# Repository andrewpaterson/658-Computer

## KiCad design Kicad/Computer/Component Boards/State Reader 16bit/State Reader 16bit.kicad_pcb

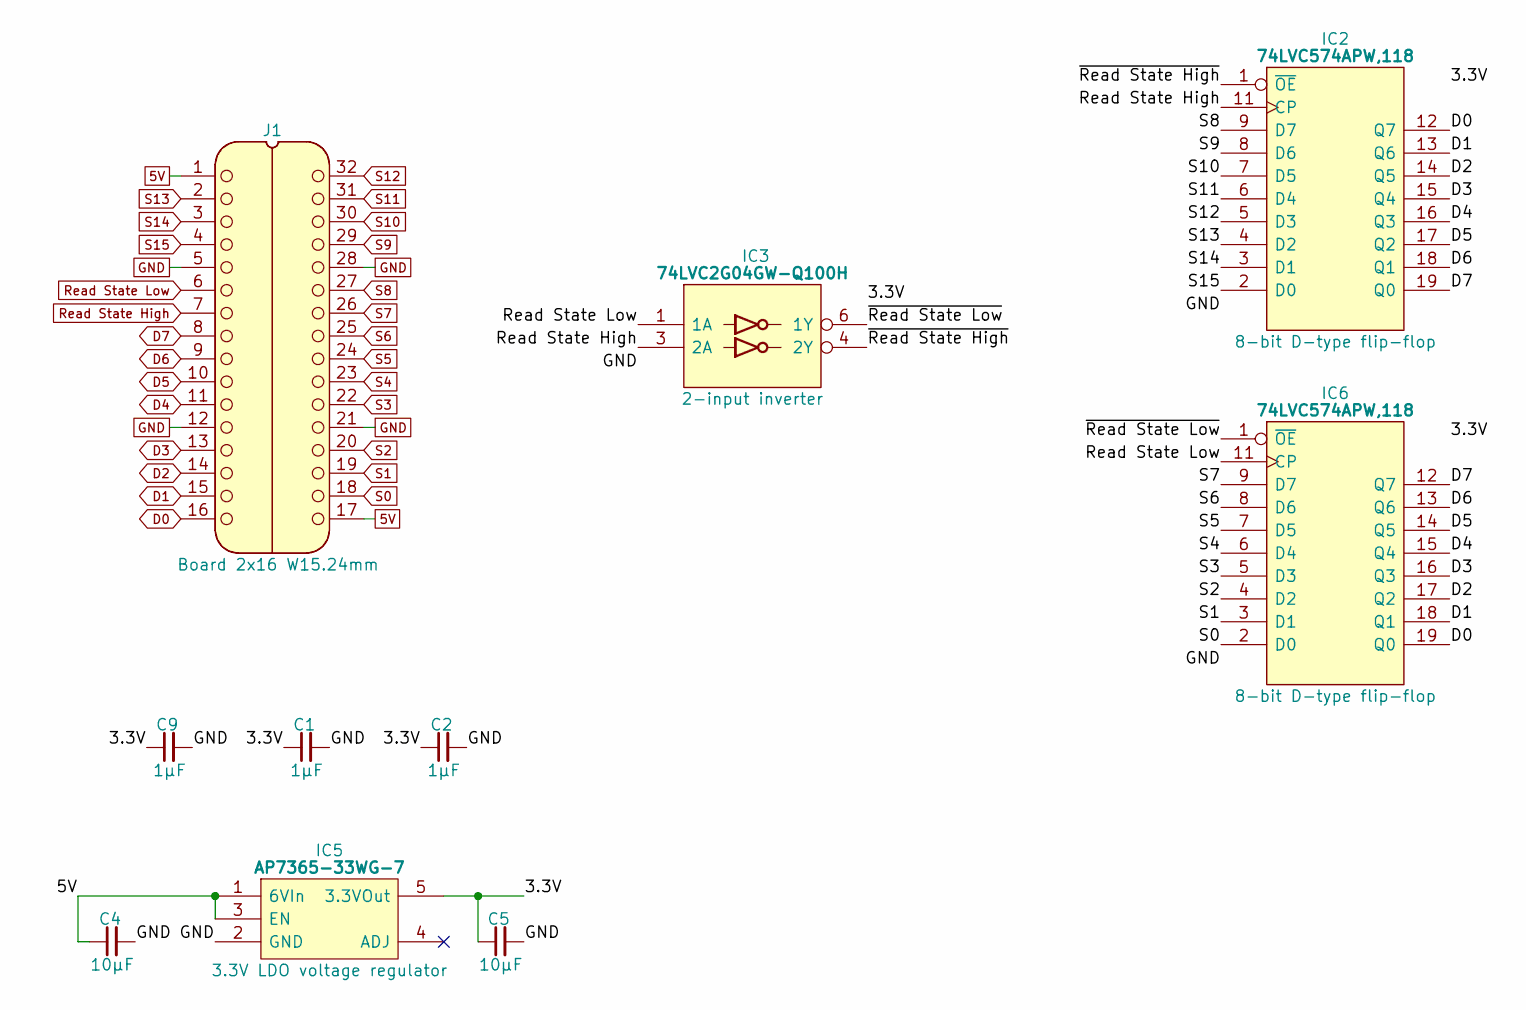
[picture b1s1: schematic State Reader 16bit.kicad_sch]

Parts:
C1, C2, C9: 1μF; C_0805
C4, C5: 10µF; C_0805
IC2, IC6: 74LVC574APW,118; SOP65P640X110-20N; Mouser Part Number 771-74LVC574APW-T
IC3: 74LVC2G04GW-Q100H; SOP65P210X110-6N; Manufacturer_Part_Number 74LVC2G04GW-Q100H; Mouser Part Number 771-74LVC2G04GWQ100H
IC5: AP7365-33WG-7; SOT95P285X130-5N; Manufacturer_Part_Number AP7365-33WG-7; Mouser Part Number 621-AP7365-33WG-7
J1: Board 2x16 W15.24mm; DIP-32_Board_W15.24mm

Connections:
5V: C4.1, IC5.1 (6VIn), IC5.3 (EN), J1.1, J1.17
/3.3V: C1.1, C2.1, C5.1, C9.1, IC2.20 (3V), IC3.5 (3V), IC5.5 (3.3VOut), IC6.20 (3V)
/~Read State High: IC2.1 (~OE), IC3.4 (2Y)
/~Read State Low: IC3.6 (1Y), IC6.1 (~OE)
D0: IC2.12 (Q7), IC6.19 (Q0), J1.16
D1: IC2.13 (Q6), IC6.18 (Q1), J1.15
D2: IC2.14 (Q5), IC6.17 (Q2), J1.14
D3: IC2.15 (Q4), IC6.16 (Q3), J1.13
D4: IC2.16 (Q3), IC6.15 (Q4), J1.11
D5: IC2.17 (Q2), IC6.14 (Q5), J1.10
D6: IC2.18 (Q1), IC6.13 (Q6), J1.9
D7: IC2.19 (Q0), IC6.12 (Q7), J1.8
GND: C1.2, C2.2, C4.2, C5.2, C9.2, IC2.10 (GND), IC3.2 (GND), IC5.2 (GND), IC6.10 (GND), J1.5, J1.12, J1.21, J1.28
Read State High: IC2.11 (CP), IC3.3 (2A), J1.7
Read State Low: IC3.1 (1A), IC6.11 (CP), J1.6
S0: IC6.2 (D0), J1.18
S1: IC6.3 (D1), J1.19
S2: IC6.4 (D2), J1.20
S3: IC6.5 (D3), J1.22
S4: IC6.6 (D4), J1.23
S5: IC6.7 (D5), J1.24
S6: IC6.8 (D6), J1.25
S7: IC6.9 (D7), J1.26
S8: IC2.9 (D7), J1.27
S9: IC2.8 (D6), J1.29
S10: IC2.7 (D5), J1.30
S11: IC2.6 (D4), J1.31
S12: IC2.5 (D3), J1.32
S13: IC2.4 (D2), J1.2
S14: IC2.3 (D1), J1.3
S15: IC2.2 (D0), J1.4

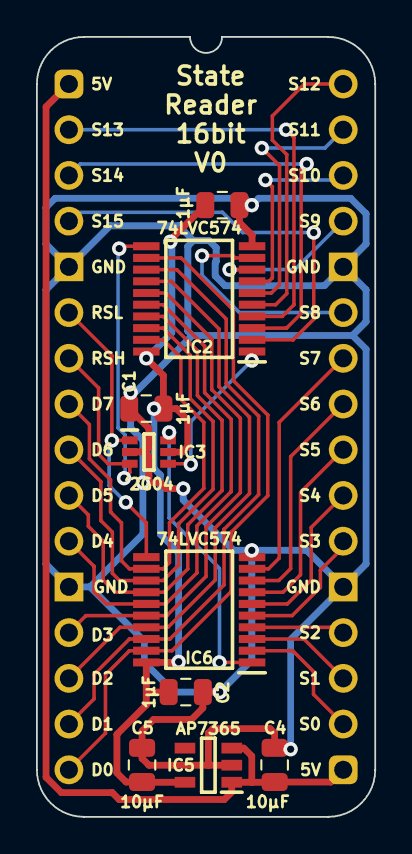
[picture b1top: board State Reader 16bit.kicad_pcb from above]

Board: 2 copper layers, 18.8 x 43.3 mm, 10 parts (0 on the bottom side), 31 nets.

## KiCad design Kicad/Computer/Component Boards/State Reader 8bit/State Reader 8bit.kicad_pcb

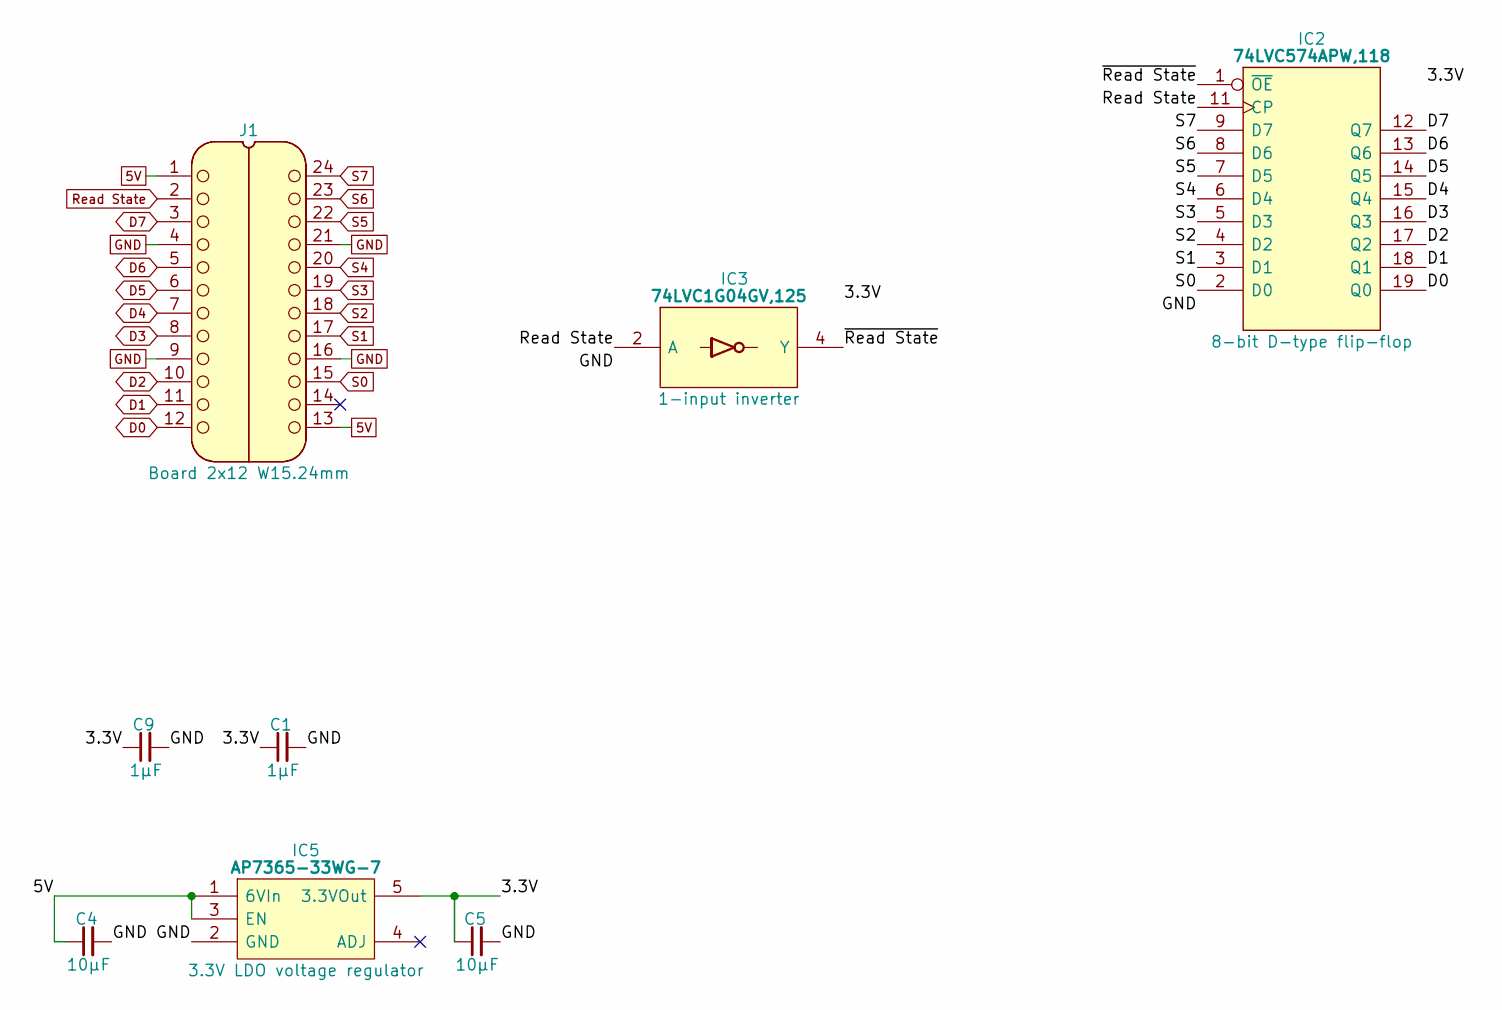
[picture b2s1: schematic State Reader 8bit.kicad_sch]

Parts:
C1, C9: 1μF; C_0805
C4, C5: 10µF; C_0805
IC2: 74LVC574APW,118; SOP65P640X110-20N; Mouser Part Number 771-74LVC574APW-T
IC3: 74LVC1G04GV,125; SOT95P275X110-5N; Manufacturer_Part_Number 74LVC1G04GV,125; Mouser Part Number 771-74LVC1G04GV
IC5: AP7365-33WG-7; SOT95P285X130-5N; Manufacturer_Part_Number AP7365-33WG-7; Mouser Part Number 621-AP7365-33WG-7
J1: Board 2x12 W15.24mm; DIP-24_Board_W15.24mm

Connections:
5V: C4.1, IC5.1 (6VIn), IC5.3 (EN), J1.1, J1.13
/3.3V: C1.1, C5.1, C9.1, IC2.20 (3V), IC5.5 (3.3VOut)
/~Read State: IC2.1 (~OE), IC3.4 (Y)
D0: IC2.19 (Q0), J1.12
D1: IC2.18 (Q1), J1.11
D2: IC2.17 (Q2), J1.10
D3: IC2.16 (Q3), J1.8
D4: IC2.15 (Q4), J1.7
D5: IC2.14 (Q5), J1.6
D6: IC2.13 (Q6), J1.5
D7: IC2.12 (Q7), J1.3
GND: C1.2, C4.2, C5.2, C9.2, IC2.10 (GND), IC3.3 (GND), IC5.2 (GND), J1.4, J1.9, J1.16, J1.21
Read State: IC2.11 (CP), IC3.2 (A), J1.2
S0: IC2.2 (D0), J1.15
S1: IC2.3 (D1), J1.17
S2: IC2.4 (D2), J1.18
S3: IC2.5 (D3), J1.19
S4: IC2.6 (D4), J1.20
S5: IC2.7 (D5), J1.22
S6: IC2.8 (D6), J1.23
S7: IC2.9 (D7), J1.24

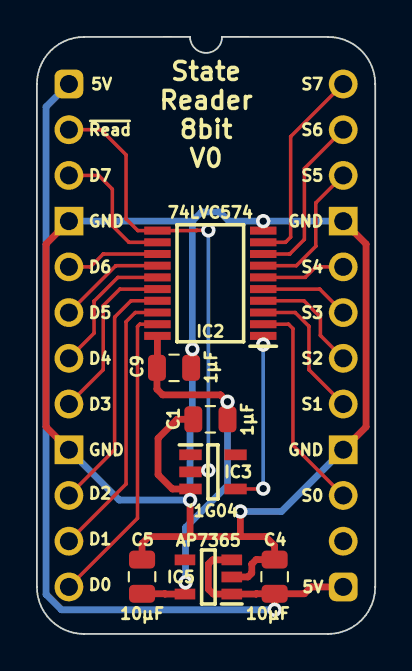
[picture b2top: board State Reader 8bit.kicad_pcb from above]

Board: 2 copper layers, 18.8 x 33.2 mm, 8 parts (0 on the bottom side), 21 nets.

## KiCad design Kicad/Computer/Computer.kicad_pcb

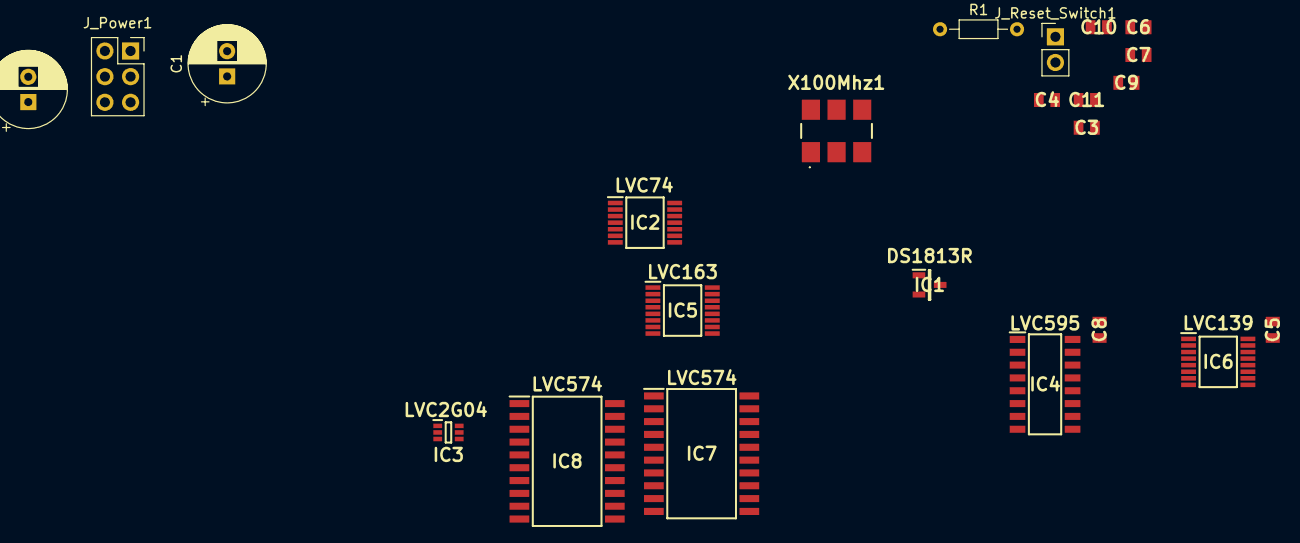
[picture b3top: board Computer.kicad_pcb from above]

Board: 2 copper layers, 23 parts (0 on the bottom side), 5 nets, no tracks yet.

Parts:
C1, C2: CP1000uF; CP_Radial_D7.5mm_P2.50mm
C3: 100pF MLCC; CAPC2012X90N
C4, C5, C6, C7, C8, C9, C10, C11: 1000pF MLCC; CAPC2012X90N
IC1: DS1813R; SOT95P237X112-3N
IC2: LVC74; SOP65P640X110-14N
IC3: LVC2G04; SOP65P210X110-6N
IC4: LVC595; SOIC127P600X175-16N
IC5: LVC163; SOP65P640X110-16N
IC6: LVC139; SOP65P640X110-16N
IC7, IC8: LVC574; SOIC127P1032X265-20N
J_Power1: Conn_02x03; PinSocket_2x03_P2.54mm_Vertical
J_Reset_Switch1: Conn_01x02_Male; PinHeader_1x02_P2.54mm_Vertical
R1: R; R_Axial_DIN0204_L3.6mm_D1.6mm_P7.62mm_Horizontal
X100Mhz1: XLH735100.000000I; XLH735100000000I

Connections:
/Timing Circuit/3.3V: C1.1, C3.1, C4.1, C5.1, C6.1, C7.1, C8.1, C9.1, C10.1, C11.1, IC2.14 (VCC), IC3.5 (VCC), IC4.16 (VCC), IC5.16 (VCC), IC6.16 (VCC), IC7.20 (VCC), IC8.20 (VCC), J_Power1.3, J_Power1.4, X100Mhz1.6 (VDD)
/Timing Circuit/5V: C2.1, IC1.2 (VCC), J_Power1.5, J_Power1.6
/Timing Circuit/GND: C1.2, C2.2, C3.2, C4.2, C5.2, C6.2, C7.2, C8.2, C9.2, C10.2, C11.2, IC1.3 (GND), J_Power1.1, J_Power1.2, R1.1
/Timing Circuit/RSTB: IC1.1 (~RST), J_Reset_Switch1.2
unnamed: J_Reset_Switch1.1, R1.2

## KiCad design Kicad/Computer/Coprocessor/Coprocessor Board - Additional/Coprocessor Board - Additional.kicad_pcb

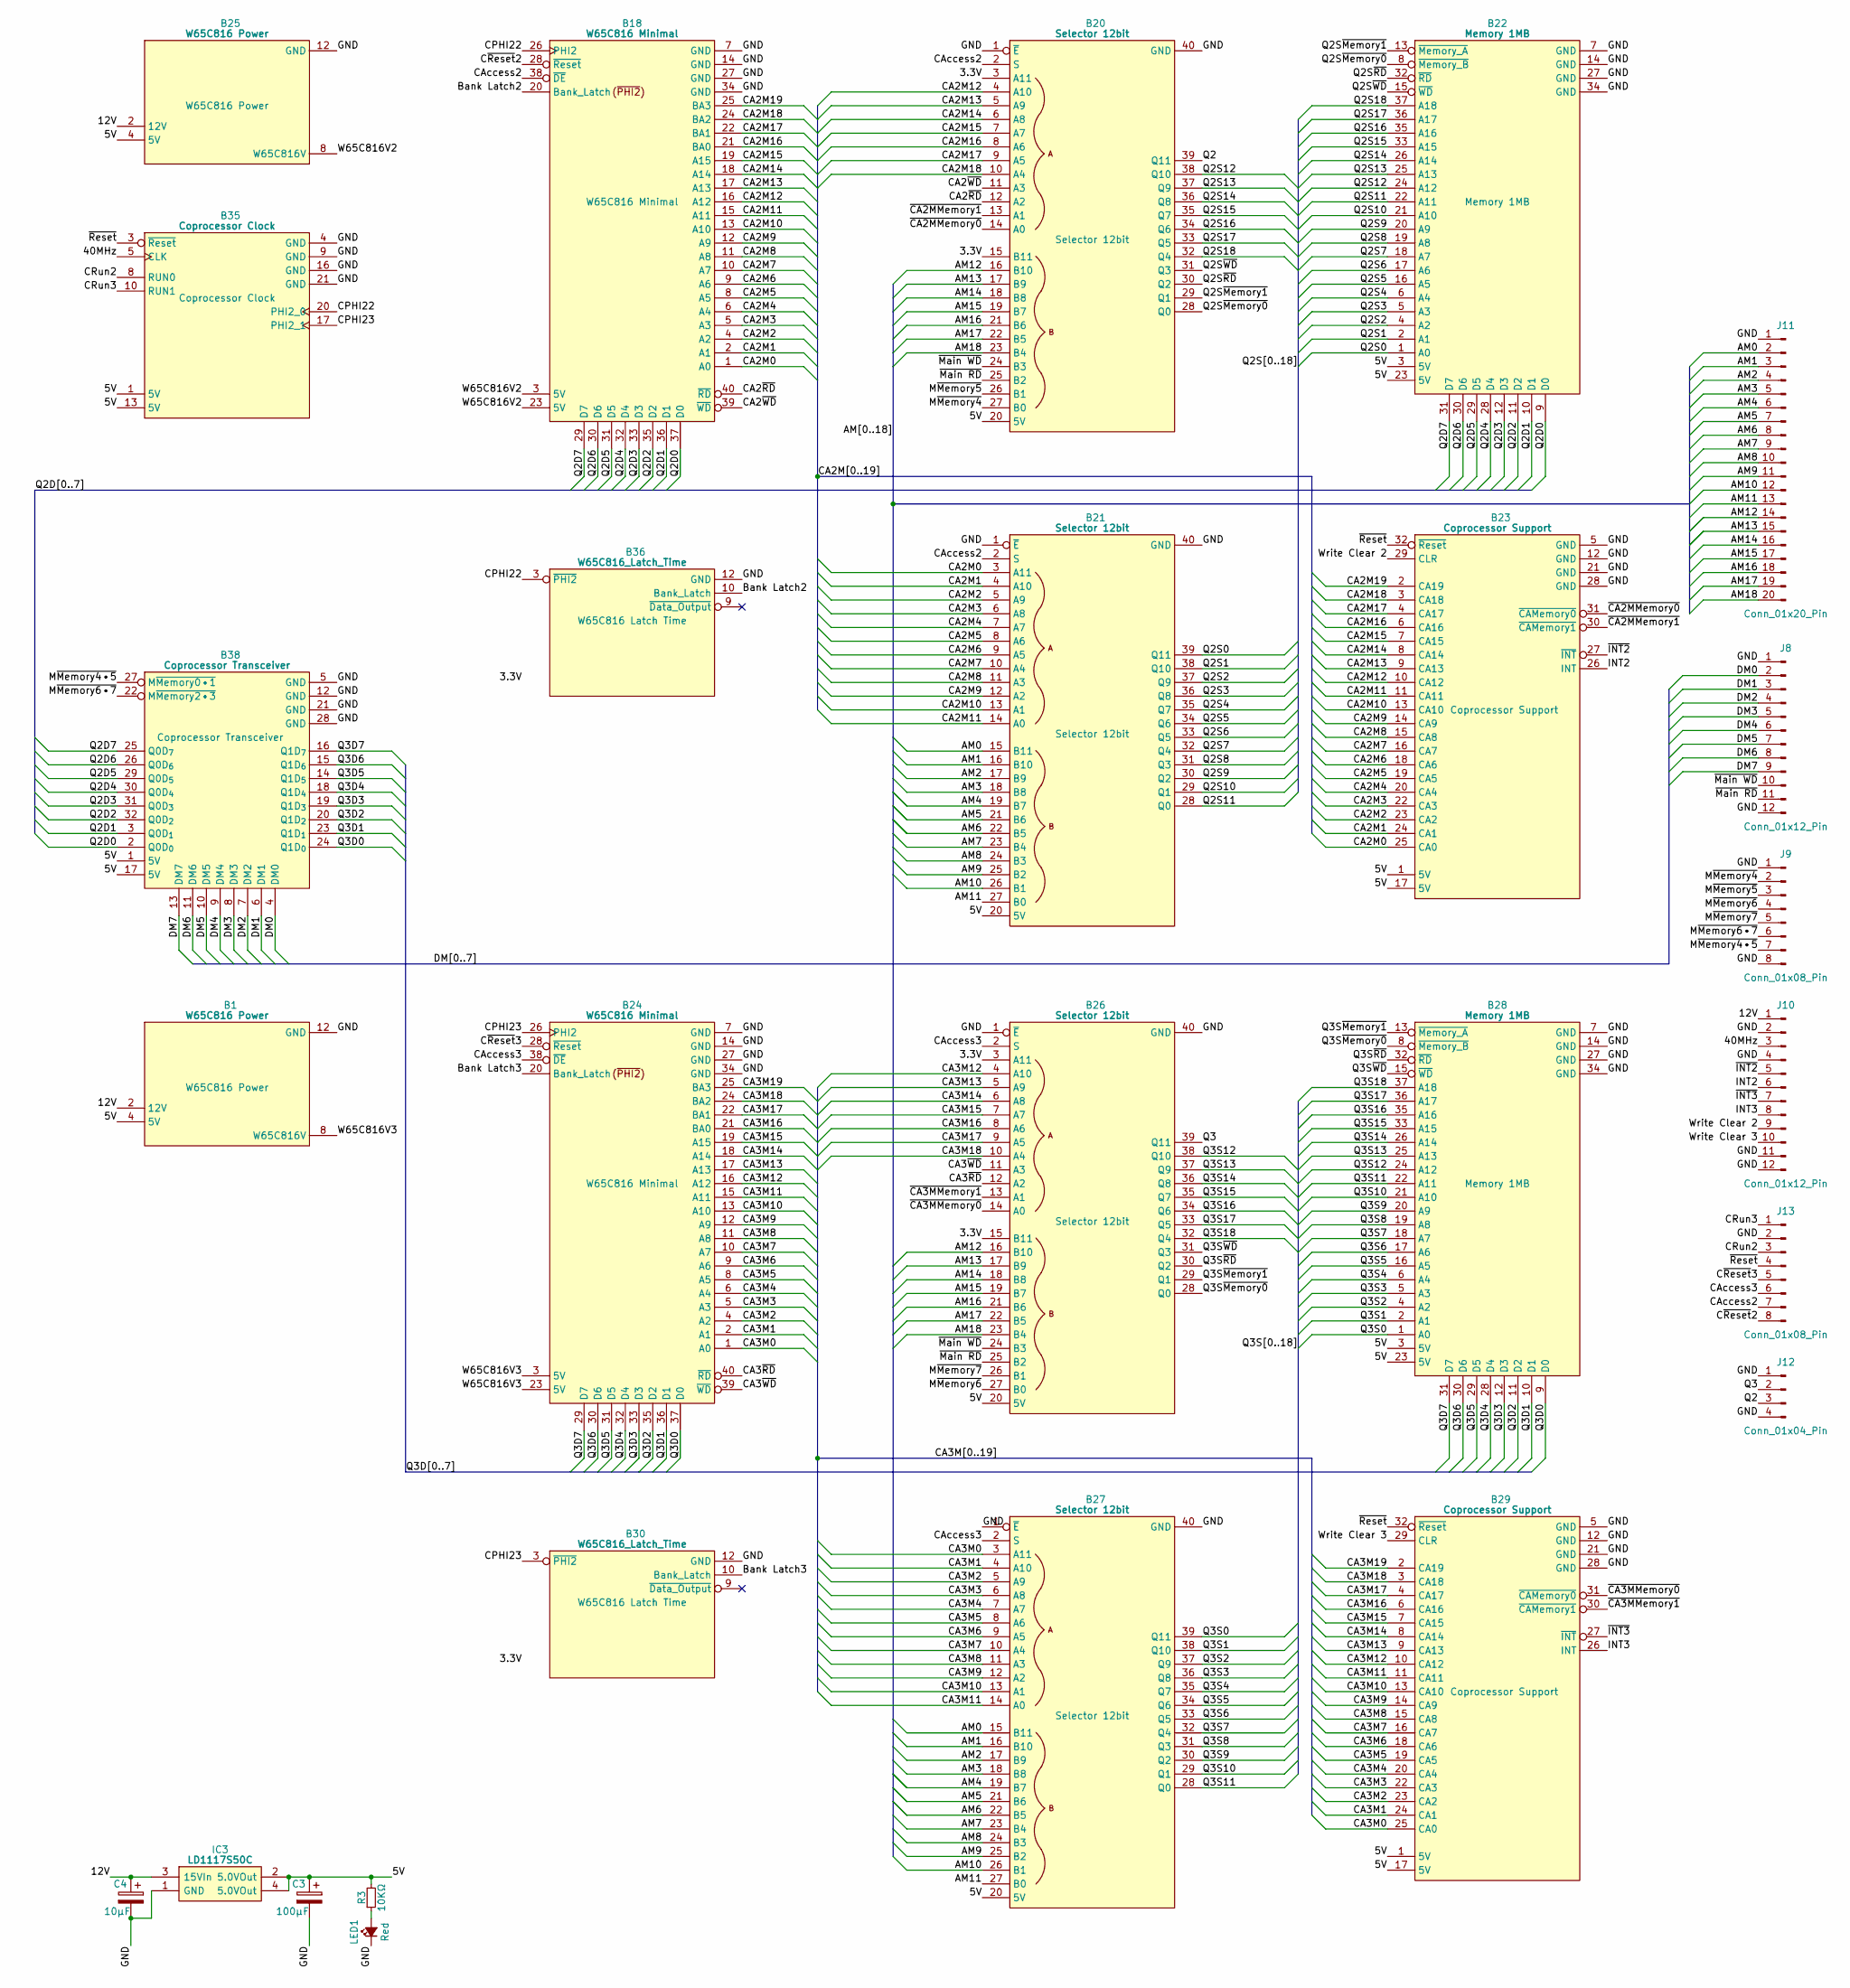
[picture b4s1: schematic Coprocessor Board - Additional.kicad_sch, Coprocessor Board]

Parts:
B1, B25: W65C816 Power; HCP65_W65C816_Power
B18, B24: W65C816 Minimal; HCP65_W65C816_Minimal
B20, B21, B26, B27: Selector 12bit; HCP65_Selector_12bit
B22, B28: Memory 1MB; HCP65_Memory_1MB
B23, B29: Coprocessor Support; HCP65_Coprocessor_Support
B30, B36: W65C816_Latch_Time; HCP65_W65C816_Latch_Time
B35: Coprocessor Clock; HCP65_Coprocessor_Clock
B38: Coprocessor Transceiver; HCP65_Coprocessor_Transceiver
C3: 100μF; CP_Radial_D4.0mm_P2.00mm
C4: 10μF; CP_Radial_D4.0mm_P2.00mm
IC3: LD1117S50C; LD1117S33C; Manufacturer_Part_Number LD1117S50C
J8, J10: Conn_01x12_Pin; PinHeader_1x12_P2.54mm_Vertical
J9, J13: Conn_01x08_Pin; PinHeader_1x08_P2.54mm_Vertical
J11: Conn_01x20_Pin; PinHeader_1x20_P2.54mm_Vertical
J12: Conn_01x04_Pin; PinHeader_1x04_P2.54mm_Vertical
LED1: Red; LED_D5.0mm
R3: 10KΩ; R_0805

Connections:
/3.3V: B20.3 (A11), B20.15 (B11), B26.3 (A11), B26.15 (B11), B30.6 (3.3V), B36.6 (3.3V)
/5V: B1.4 (5V), B20.20 (5V), B21.20 (5V), B22.3 (5V), B22.23 (5V), B23.1 (5V), B23.17 (5V), B25.4 (5V), B26.20 (5V), B27.20 (5V), B28.3 (5V), B28.23 (5V), B29.1 (5V), B29.17 (5V), B35.1 (5V), B35.13 (5V), B38.1 (5V), B38.17 (5V), C3.1, IC3.2 (5.0VOut), IC3.4 (5.0VOut), R3.2
/12V: B1.2 (12V), B25.2 (12V), C4.1, IC3.3 (15VIn), J10.1
/40MHz: B35.5 (CLK), J10.3
/AM0: B21.15 (B11), B27.15 (B11), J11.2
/AM1: B21.16 (B10), B27.16 (B10), J11.3
/AM2: B21.17 (B9), B27.17 (B9), J11.4
/AM3: B21.18 (B8), B27.18 (B8), J11.5
/AM4: B21.19 (B7), B27.19 (B7), J11.6
/AM5: B21.21 (B6), B27.21 (B6), J11.7
/AM6: B21.22 (B5), B27.22 (B5), J11.8
/AM7: B21.23 (B4), B27.23 (B4), J11.9
/AM8: B21.24 (B3), B27.24 (B3), J11.10
/AM9: B21.25 (B2), B27.25 (B2), J11.11
/AM10: B21.26 (B1), B27.26 (B1), J11.12
/AM11: B21.27 (B0), B27.27 (B0), J11.13
/AM12: B20.16 (B10), B26.16 (B10), J11.14
/AM13: B20.17 (B9), B26.17 (B9), J11.15
/AM14: B20.18 (B8), B26.18 (B8), J11.16
/AM15: B20.19 (B7), B26.19 (B7), J11.17
/AM16: B20.21 (B6), B26.21 (B6), J11.18
/AM17: B20.22 (B5), B26.22 (B5), J11.19
/AM18: B20.23 (B4), B26.23 (B4), J11.20
/Bank Latch2: B18.20 (Bank_Latch), B36.10 (Bank_Latch)
/Bank Latch3: B24.20 (Bank_Latch), B30.10 (Bank_Latch)
/CA2M0: B18.1 (A0), B21.3 (A11), B23.25 (CA0)
/CA2M1: B18.2 (A1), B21.4 (A10), B23.24 (CA1)
/CA2M2: B18.4 (A2), B21.5 (A9), B23.23 (CA2)
/CA2M3: B18.5 (A3), B21.6 (A8), B23.22 (CA3)
/CA2M4: B18.6 (A4), B21.7 (A7), B23.20 (CA4)
/CA2M5: B18.8 (A5), B21.8 (A6), B23.19 (CA5)
/CA2M6: B18.9 (A6), B21.9 (A5), B23.18 (CA6)
/CA2M7: B18.10 (A7), B21.10 (A4), B23.16 (CA7)
/CA2M8: B18.11 (A8), B21.11 (A3), B23.15 (CA8)
/CA2M9: B18.12 (A9), B21.12 (A2), B23.14 (CA9)
/CA2M10: B18.13 (A10), B21.13 (A1), B23.13 (CA10)
/CA2M11: B18.15 (A11), B21.14 (A0), B23.11 (CA11)
/CA2M12: B18.16 (A12), B20.4 (A10), B23.10 (CA12)
/CA2M13: B18.17 (A13), B20.5 (A9), B23.9 (CA13)
/CA2M14: B18.18 (A14), B20.6 (A8), B23.8 (CA14)
/CA2M15: B18.19 (A15), B20.7 (A7), B23.7 (CA15)
/CA2M16: B18.21 (BA0), B20.8 (A6), B23.6 (CA16)
/CA2M17: B18.22 (BA1), B20.9 (A5), B23.4 (CA17)
/CA2M18: B18.24 (BA2), B20.10 (A4), B23.3 (CA18)
/CA2M19: B18.25 (BA3), B23.2 (CA19)
/CA2~RD: B18.40 (~RD), B20.12 (A2)
/CA2~WD: B18.39 (~WD), B20.11 (A3)
/CA3M0: B24.1 (A0), B27.3 (A11), B29.25 (CA0)
/CA3M1: B24.2 (A1), B27.4 (A10), B29.24 (CA1)
/CA3M2: B24.4 (A2), B27.5 (A9), B29.23 (CA2)
/CA3M3: B24.5 (A3), B27.6 (A8), B29.22 (CA3)
/CA3M4: B24.6 (A4), B27.7 (A7), B29.20 (CA4)
/CA3M5: B24.8 (A5), B27.8 (A6), B29.19 (CA5)
/CA3M6: B24.9 (A6), B27.9 (A5), B29.18 (CA6)
/CA3M7: B24.10 (A7), B27.10 (A4), B29.16 (CA7)
/CA3M8: B24.11 (A8), B27.11 (A3), B29.15 (CA8)
/CA3M9: B24.12 (A9), B27.12 (A2), B29.14 (CA9)
/CA3M10: B24.13 (A10), B27.13 (A1), B29.13 (CA10)
/CA3M11: B24.15 (A11), B27.14 (A0), B29.11 (CA11)
/CA3M12: B24.16 (A12), B26.4 (A10), B29.10 (CA12)
/CA3M13: B24.17 (A13), B26.5 (A9), B29.9 (CA13)
/CA3M14: B24.18 (A14), B26.6 (A8), B29.8 (CA14)
/CA3M15: B24.19 (A15), B26.7 (A7), B29.7 (CA15)
/CA3M16: B24.21 (BA0), B26.8 (A6), B29.6 (CA16)
/CA3M17: B24.22 (BA1), B26.9 (A5), B29.4 (CA17)
/CA3M18: B24.24 (BA2), B26.10 (A4), B29.3 (CA18)
/CA3M19: B24.25 (BA3), B29.2 (CA19)
/CA3~RD: B24.40 (~RD), B26.12 (A2)
/CA3~WD: B24.39 (~WD), B26.11 (A3)
/CAccess2: B18.38 (~DE), B20.2 (S), B21.2 (S), J13.7
/CAccess3: B24.38 (~DE), B26.2 (S), B27.2 (S), J13.6
/CPHI22: B18.26 (PHI2), B35.20 (PHI2_0), B36.3 (~PHI2)
/CPHI23: B24.26 (PHI2), B30.3 (~PHI2), B35.17 (PHI2_1)
/CRun2: B35.8 (RUN0), J13.3
/CRun3: B35.10 (RUN1), J13.1
/C~Reset2: B18.28 (~Reset), J13.8
/C~Reset3: B24.28 (~Reset), J13.5
/DM0: B38.4 (DM0), J8.2
/DM1: B38.6 (DM1), J8.3
/DM2: B38.7 (DM2), J8.4
/DM3: B38.8 (DM3), J8.5
/DM4: B38.9 (DM4), J8.6
/DM5: B38.10 (DM5), J8.7
/DM6: B38.11 (DM6), J8.8
/DM7: B38.13 (DM7), J8.9
/GND: B1.12 (GND), B18.7 (GND), B18.14 (GND), B18.27 (GND), B18.34 (GND), B20.1 (~E), B20.40 (GND), B21.1 (~E), B21.40 (GND), B22.7 (GND), B22.14 (GND), B22.27 (GND), B22.34 (GND), B23.5 (GND), B23.12 (GND), B23.21 (GND), B23.28 (GND), B24.7 (GND), B24.14 (GND), B24.27 (GND), B24.34 (GND), B25.12 (GND), B26.1 (~E), B26.40 (GND), B27.1 (~E), B27.40 (GND), B28.7 (GND), B28.14 (GND), B28.27 (GND), B28.34 (GND), B29.5 (GND), B29.12 (GND), B29.21 (GND), B29.28 (GND), B30.12 (GND), B35.4 (GND), B35.9 (GND), B35.16 (GND), B35.21 (GND), B36.12 (GND), B38.5 (GND), B38.12 (GND), B38.21 (GND), B38.28 (GND), C3.2, C4.2, IC3.1 (GND), J8.1, J8.12, J9.1, J9.8, J10.2, J10.4, J10.11, J10.12, J11.1, J12.1, J12.4, J13.2, LED1.1 (K)
/INT2: B23.26 (INT), J10.6
/INT3: B29.26 (INT), J10.8
/M~Memory4: B20.27 (B0), J9.2
/M~Memory4•5: B38.27 (M~Memory0•1), J9.7
/M~Memory5: B20.26 (B1), J9.3
/M~Memory6: B26.27 (B0), J9.4
/M~Memory6•7: B38.22 (M~Memory2•3), J9.6
/M~Memory7: B26.26 (B1), J9.5
/Q2: B20.39 (Q11), J12.3
/Q2D0: B18.37 (D0), B22.9 (D0), B38.2 (Q0D_{0})
/Q2D1: B18.36 (D1), B22.10 (D1), B38.3 (Q0D_{1})
/Q2D2: B18.35 (D2), B22.11 (D2), B38.32 (Q0D_{2})
/Q2D3: B18.33 (D3), B22.12 (D3), B38.31 (Q0D_{3})
/Q2D4: B18.32 (D4), B22.28 (D4), B38.30 (Q0D_{4})
/Q2D5: B18.31 (D5), B22.29 (D5), B38.29 (Q0D_{5})
/Q2D6: B18.30 (D6), B22.30 (D6), B38.26 (Q0D_{6})
/Q2D7: B18.29 (D7), B22.31 (D7), B38.25 (Q0D_{7})
/Q2S0: B21.39 (Q11), B22.1 (A0)
/Q2S1: B21.38 (Q10), B22.2 (A1)
/Q2S2: B21.37 (Q9), B22.4 (A2)
/Q2S3: B21.36 (Q8), B22.5 (A3)
/Q2S4: B21.35 (Q7), B22.6 (A4)
/Q2S5: B21.34 (Q6), B22.16 (A5)
/Q2S6: B21.33 (Q5), B22.17 (A6)
/Q2S7: B21.32 (Q4), B22.18 (A7)
/Q2S8: B21.31 (Q3), B22.19 (A8)
/Q2S9: B21.30 (Q2), B22.20 (A9)
/Q2S10: B21.29 (Q1), B22.21 (A10)
/Q2S11: B21.28 (Q0), B22.22 (A11)
/Q2S12: B20.38 (Q10), B22.24 (A12)
/Q2S13: B20.37 (Q9), B22.25 (A13)
/Q2S14: B20.36 (Q8), B22.26 (A14)
/Q2S15: B20.35 (Q7), B22.33 (A15)
/Q2S16: B20.34 (Q6), B22.35 (A16)
/Q2S17: B20.33 (Q5), B22.36 (A17)
/Q2S18: B20.32 (Q4), B22.37 (A18)
/Q2S~Memory0: B20.28 (Q0), B22.8 (~Memory_B)
/Q2S~Memory1: B20.29 (Q1), B22.13 (~Memory_A)
/Q2S~RD: B20.30 (Q2), B22.32 (~RD)
/Q2S~WD: B20.31 (Q3), B22.15 (~WD)
/Q3: B26.39 (Q11), J12.2
/Q3D0: B24.37 (D0), B28.9 (D0), B38.24 (Q1D_{0})
/Q3D1: B24.36 (D1), B28.10 (D1), B38.23 (Q1D_{1})
/Q3D2: B24.35 (D2), B28.11 (D2), B38.20 (Q1D_{2})
/Q3D3: B24.33 (D3), B28.12 (D3), B38.19 (Q1D_{3})
/Q3D4: B24.32 (D4), B28.28 (D4), B38.18 (Q1D_{4})
/Q3D5: B24.31 (D5), B28.29 (D5), B38.14 (Q1D_{5})
/Q3D6: B24.30 (D6), B28.30 (D6), B38.15 (Q1D_{6})
/Q3D7: B24.29 (D7), B28.31 (D7), B38.16 (Q1D_{7})
/Q3S0: B27.39 (Q11), B28.1 (A0)
/Q3S1: B27.38 (Q10), B28.2 (A1)
/Q3S2: B27.37 (Q9), B28.4 (A2)
/Q3S3: B27.36 (Q8), B28.5 (A3)
/Q3S4: B27.35 (Q7), B28.6 (A4)
/Q3S5: B27.34 (Q6), B28.16 (A5)
/Q3S6: B27.33 (Q5), B28.17 (A6)
/Q3S7: B27.32 (Q4), B28.18 (A7)
/Q3S8: B27.31 (Q3), B28.19 (A8)
/Q3S9: B27.30 (Q2), B28.20 (A9)
/Q3S10: B27.29 (Q1), B28.21 (A10)
/Q3S11: B27.28 (Q0), B28.22 (A11)
/Q3S12: B26.38 (Q10), B28.24 (A12)
/Q3S13: B26.37 (Q9), B28.25 (A13)
/Q3S14: B26.36 (Q8), B28.26 (A14)
/Q3S15: B26.35 (Q7), B28.33 (A15)
/Q3S16: B26.34 (Q6), B28.35 (A16)
/Q3S17: B26.33 (Q5), B28.36 (A17)
/Q3S18: B26.32 (Q4), B28.37 (A18)
/Q3S~Memory0: B26.28 (Q0), B28.8 (~Memory_B)
/Q3S~Memory1: B26.29 (Q1), B28.13 (~Memory_A)
/Q3S~RD: B26.30 (Q2), B28.32 (~RD)
/Q3S~WD: B26.31 (Q3), B28.15 (~WD)
/W65C816V2: B18.3 (5V), B18.23 (5V), B25.8 (W65C816V)
/W65C816V3: B1.8 (W65C816V), B24.3 (5V), B24.23 (5V)
/Write Clear 2: B23.29 (CLR), J10.9
/Write Clear 3: B29.29 (CLR), J10.10
/~CA2MMemory0: B20.14 (A0), B23.31 (~CAMemory0)
/~CA2MMemory1: B20.13 (A1), B23.30 (~CAMemory1)
/~CA3MMemory0: B26.14 (A0), B29.31 (~CAMemory0)
/~CA3MMemory1: B26.13 (A1), B29.30 (~CAMemory1)
/~INT2: B23.27 (~INT), J10.5
/~INT3: B29.27 (~INT), J10.7
/~Main RD: B20.25 (B2), B26.25 (B2), J8.11
/~Main WD: B20.24 (B3), B26.24 (B3), J8.10
/~Reset: B23.32 (~Reset), B29.32 (~Reset), B35.3 (~Reset), J13.4
unnamed: LED1.2 (A), R3.1

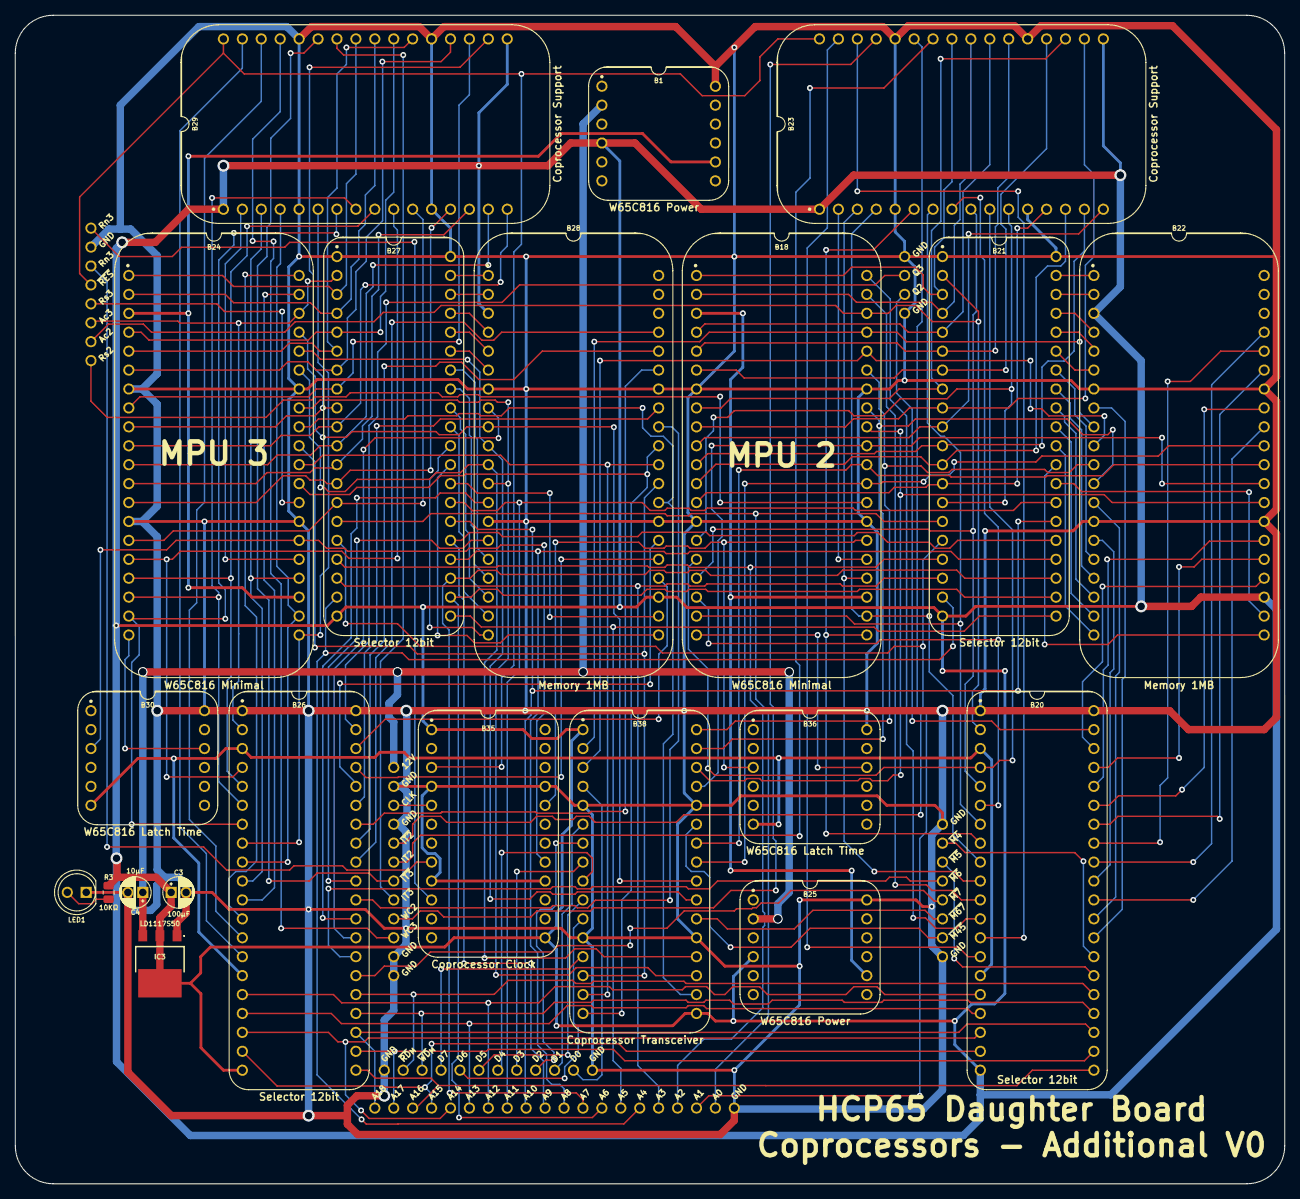
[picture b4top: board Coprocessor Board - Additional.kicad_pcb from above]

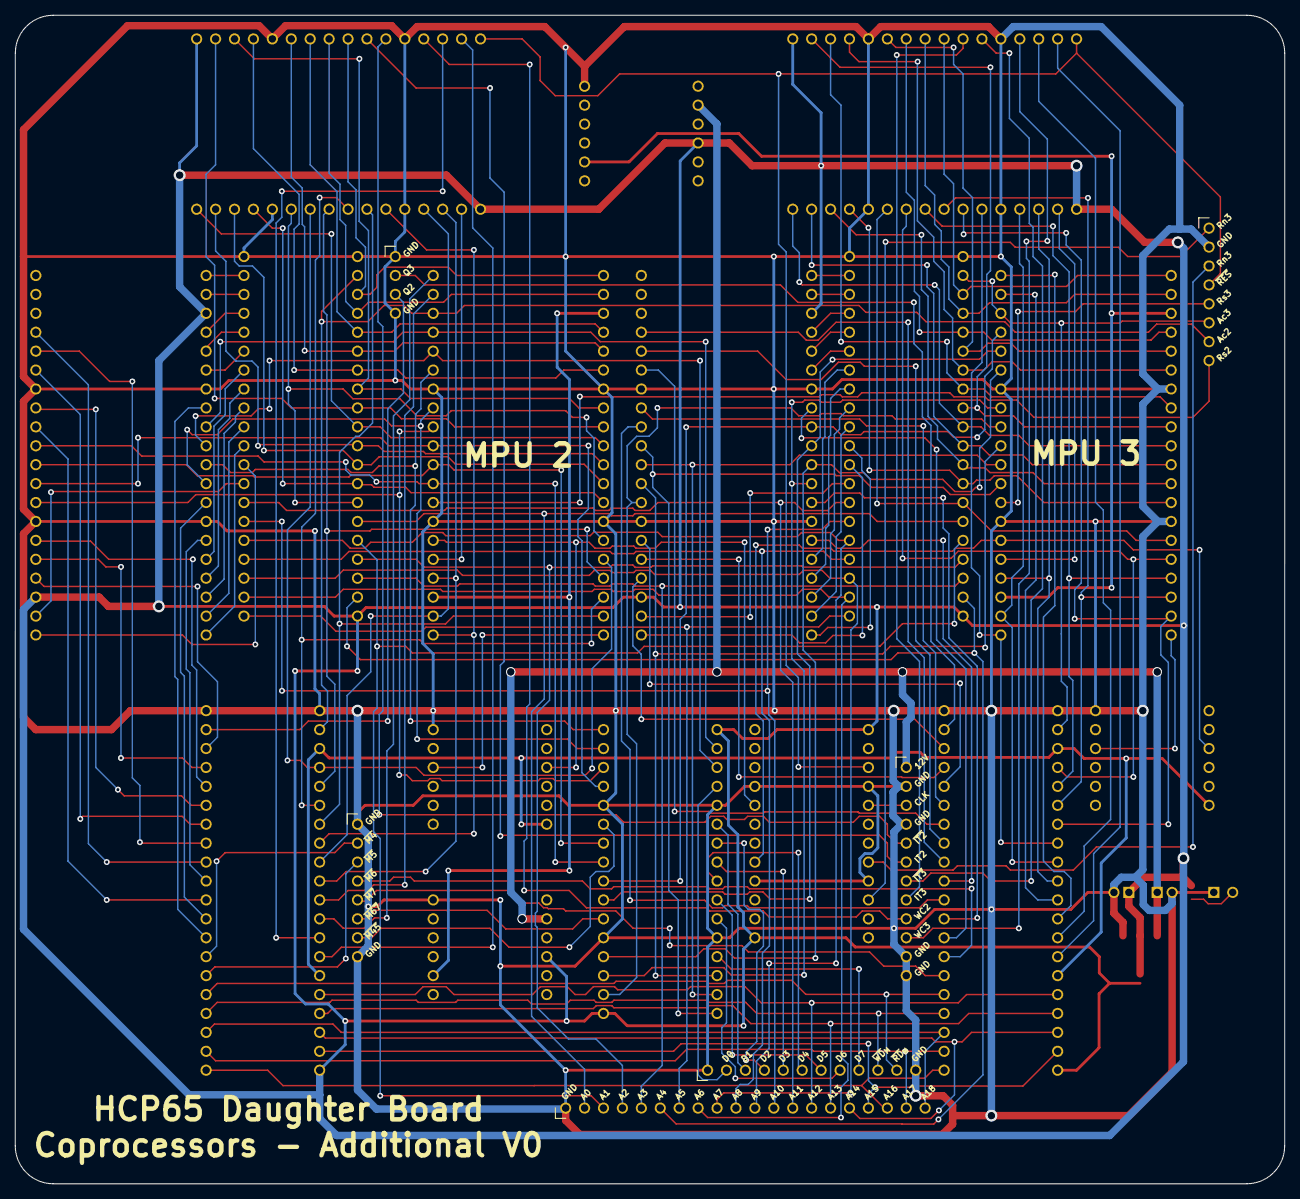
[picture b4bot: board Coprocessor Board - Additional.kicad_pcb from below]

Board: 2 copper layers, 170.4 x 156.8 mm, 27 parts (6 on the bottom side), 172 nets.
